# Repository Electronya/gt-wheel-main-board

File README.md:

# gt-wheel-main-board
GT DIY Wheel Main Board

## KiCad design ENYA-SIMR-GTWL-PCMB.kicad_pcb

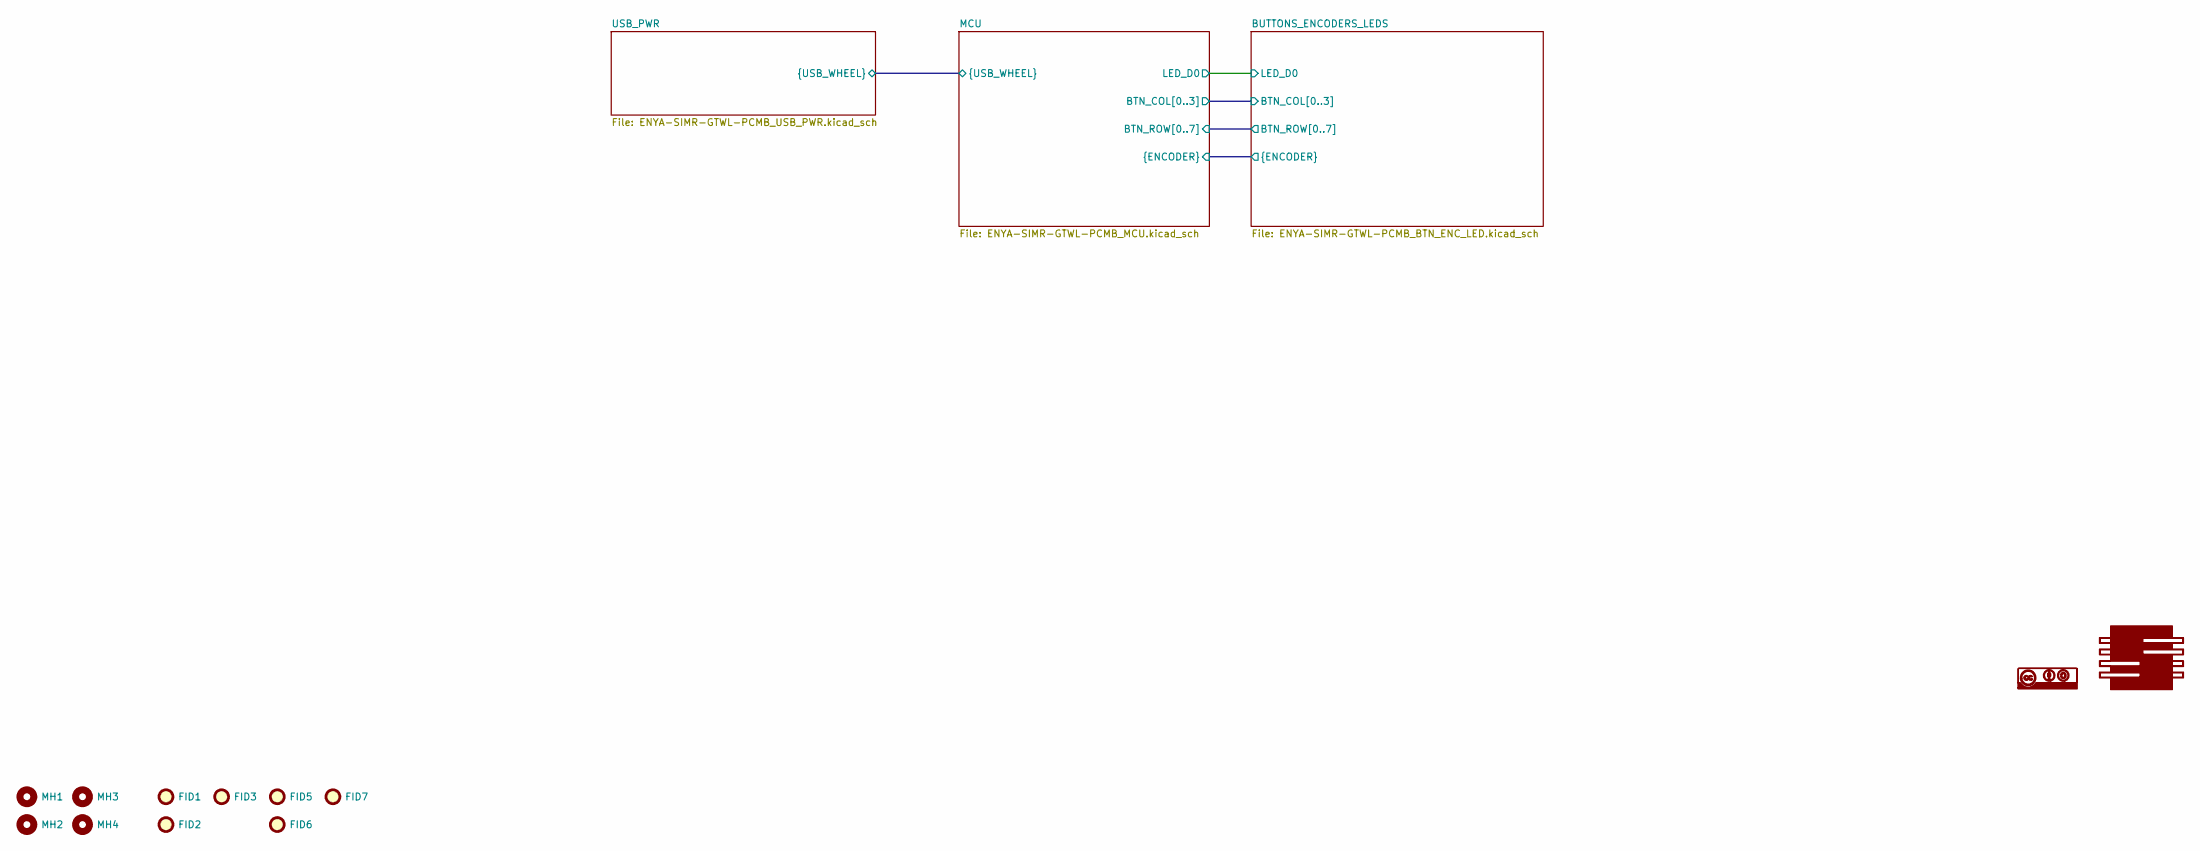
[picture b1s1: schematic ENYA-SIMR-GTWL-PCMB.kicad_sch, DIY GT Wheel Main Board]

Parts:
FID1, FID2, FID3, FID5, FID6, FID7: Fiducial; Fiducial_1.5mm_Mask3mm
G1: Electronya_Logo; Electronya_Logo_12MM
G2: CC-BY-SA_Logo; CC-BY-SA_10MM
MH1, MH2, MH3, MH4: MH-NPLTD-M3; MountingHole_3.2mm_M3_DIN965

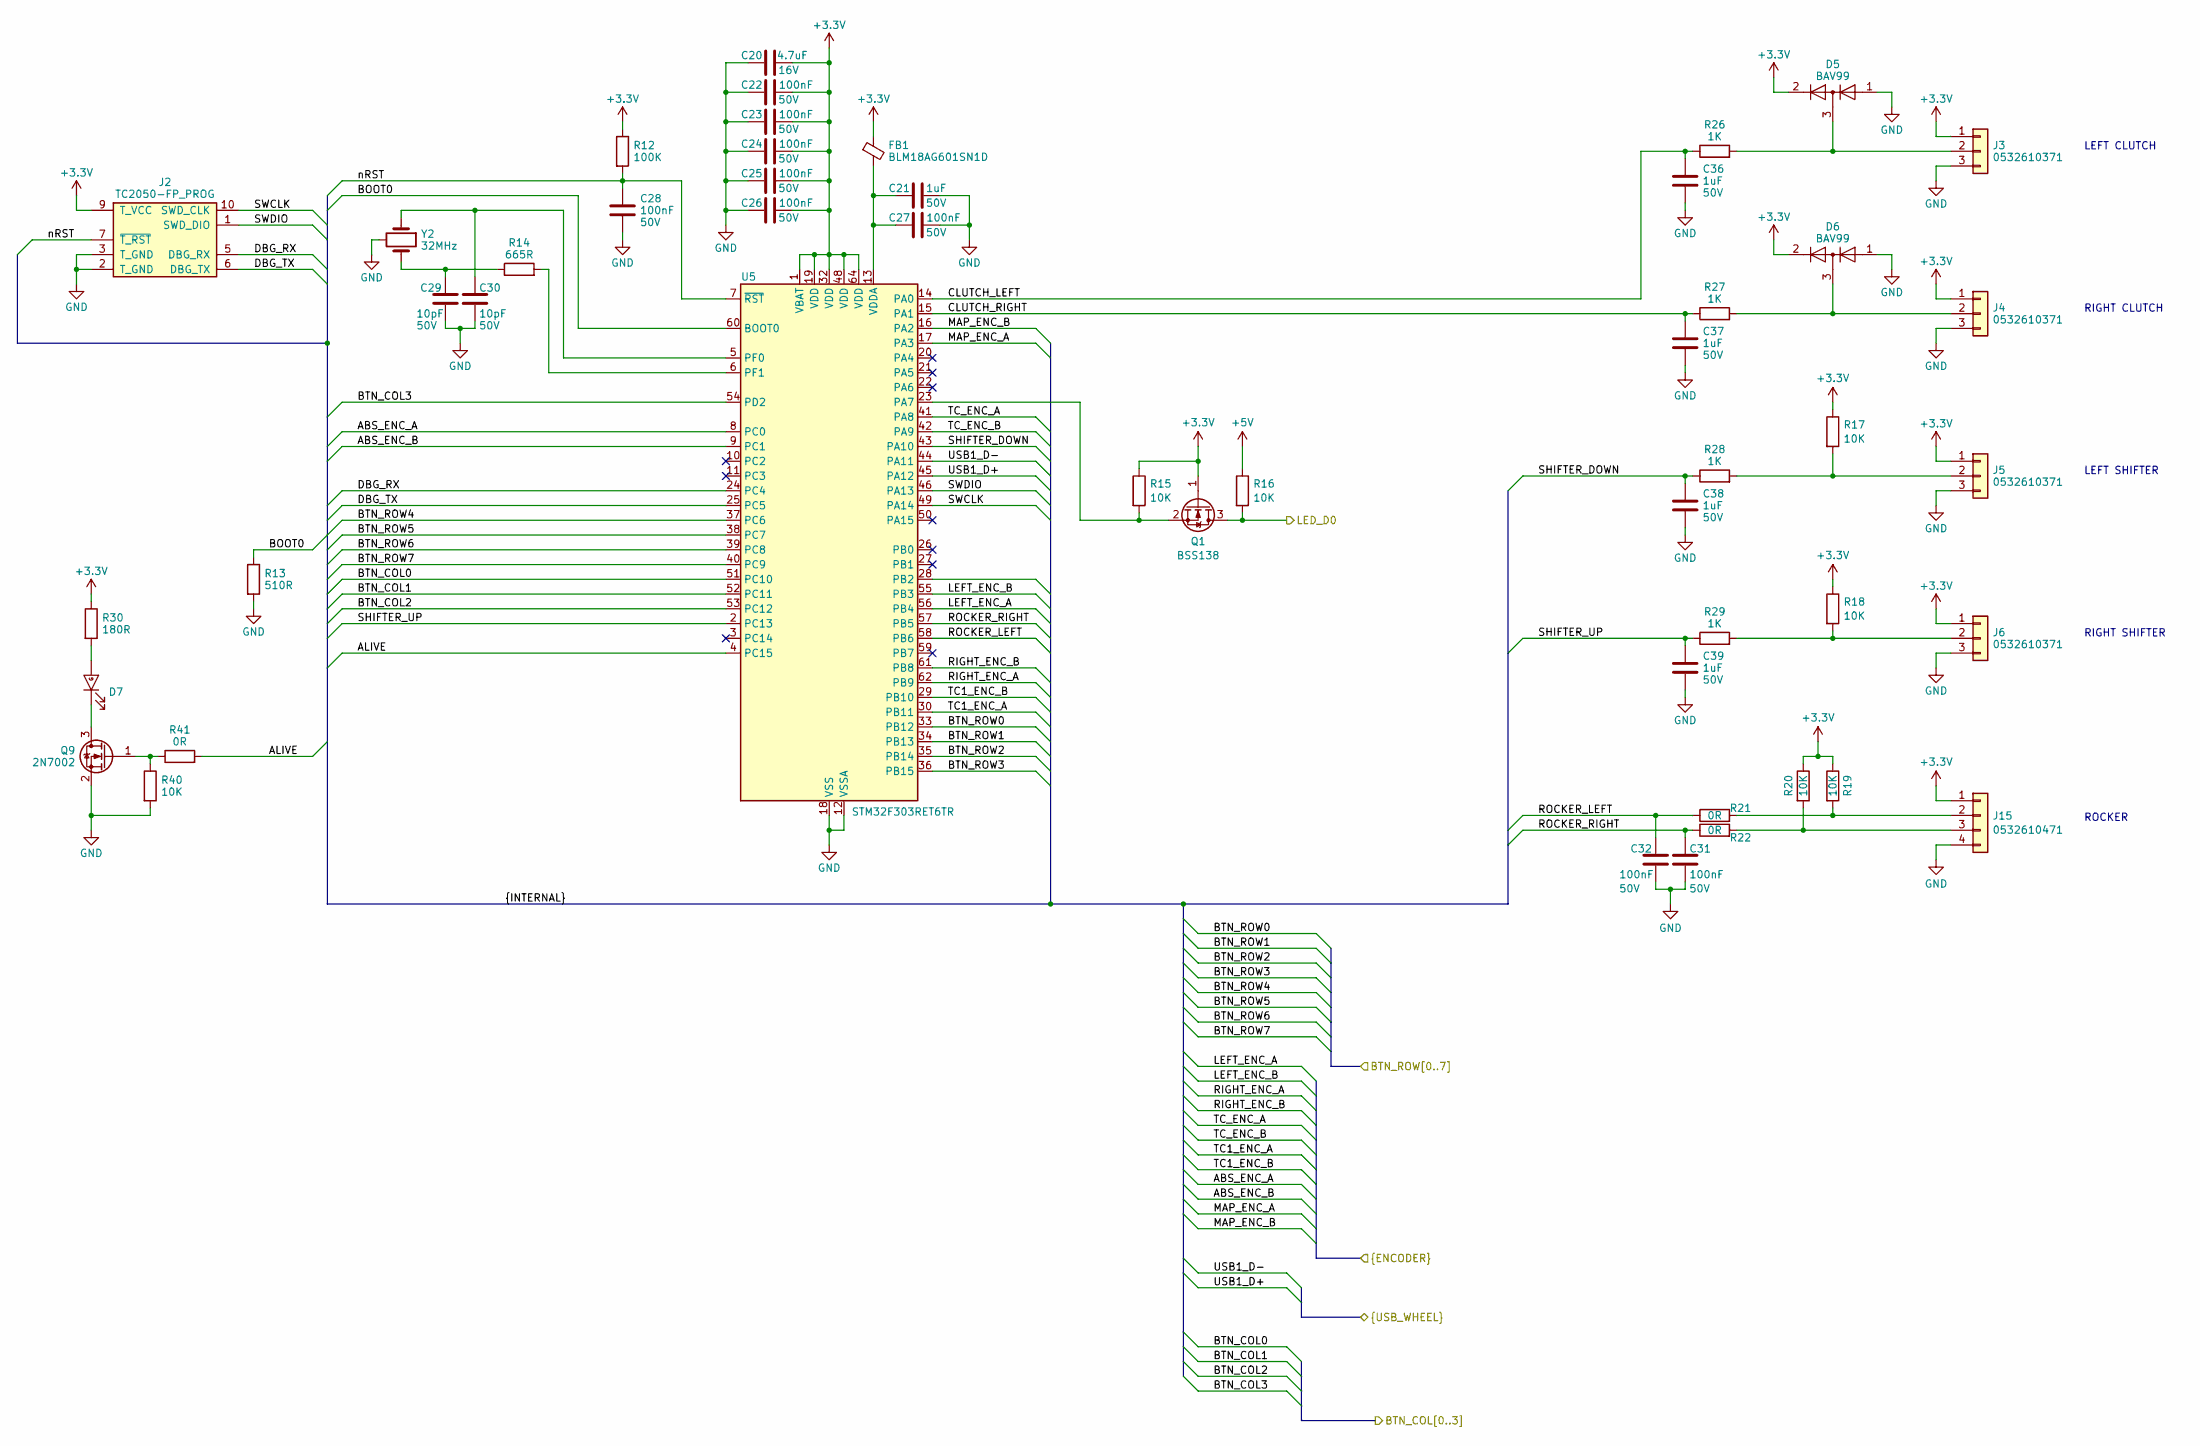
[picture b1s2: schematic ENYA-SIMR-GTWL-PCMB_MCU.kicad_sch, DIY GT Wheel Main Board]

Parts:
C20: 4.7uF_CER_0805_16V; C_0805_2012Metric; Voltage Rating 16V; Manufacturer Part Number CL21B475KOFNNNE; Digi-Key Part Number 1276-2873-1-ND
C21, C36, C37, C38, C39: 1uF_CER_0603_50V; C_0603_1608Metric; Voltage Rating 50V; Manufacturer Part Number UMK107BJ105KA-T; Digi-Key Part Number 587-2400-1-ND
C22, C23, C24, C25, C26, C27, C28, C31, C32: 100nF_CER_0603_50V; C_0603_1608Metric; Voltage Rating 50V; Manufacturer Part Number 06033D104MAT2A; Digi-Key Part Number 478-7905-1-ND
C29, C30: 10pF_CER_0603_50V; C_0603_1608Metric; Voltage Rating 50V; Manufacturer Part Number 06035A100JAT2A; Digi-Key Part Number 478-1163-1-ND
D5: BAV99; SOT-23
D6: BAV99_SOT-23; SOT-23; Manufacturer Part Number BAV99; Digi-Key Part Number 1655-BAV99CT-ND
D7: GRN_SMD_0603_0.3H; LED_0603_1608Metric; Manufacturer Part Number 150060GS73220; Digi-Key Part Number 732-11995-1-ND
FB1: 600R_100MHz_0R38_0603; L_0603_1608Metric; Manufacturer Part Number BLM18AG601SN1D; Digi-Key Part Number 490-1014-1-ND
J2: TC2050-FP_PROG; Tag-Connect_TC2050-IDC-FP_2x05_P1.27mm_Vertical; Manufacturer Part Number TC2050-FP
J3, J4, J5, J6: PICO_BLADE_1x3_MALE_RA_SMD; PICO_BLADE_53261_1x3_SMD_RA_1.25MM; Manufacturer Part Number 0532610371; Digi-Key Part Number WM7621CT-ND
J15: PICO_BLADE_1x4_MALE_RA_SMD; PICO_BLADE_53261_1x4_SMD_RA_1.25MM; Manufacturer Part Number 0532610471; Digi-Key Part Number WM7622CT-ND
Q1: BSS138; SOT-23; Manufacturer Part Number BSS138; Digi-Key Part Number BSS138CT-ND
Q9: 2N7002; SOT-23; Manufacturer Part Number 2N7002; Digi-Key Part Number 2N7002NCT-ND
R12: 100K_0603_100MW; R_0603_1608Metric; Manufacturer Part Number RC0603FR-07100KL; Digi-Key Part Number 311-100KHRCT-ND
R13: 510R_0603_100MW; R_0603_1608Metric; Manufacturer Part Number RC0603FR-07510RL; Digi-Key Part Number 311-510HRCT-ND
R14: 665R_0603_100MW; R_0603_1608Metric; Manufacturer Part Number RC0603FR-07665RL; Digi-Key Part Number 311-665HRCT-ND
R15, R16, R17, R18, R19, R20, R40: 10K_0603_100MW; R_0603_1608Metric; Manufacturer Part Number ERJ-3EKF1002V; Digi-Key Part Number P10.0KHCT-ND
R21, R22, R41: 0R_0603_100MW; R_0603_1608Metric; Manufacturer Part Number ERJ-3GEY0R00V; Digi-Key Part Number P0.0GCT-ND
R26, R27, R28, R29: 1K_0603_100MW; R_0603_1608Metric; Manufacturer Part Number ERJ-3EKF1001V; Digi-Key Part Number P1.00KHCT-ND
R30: 180R_0603_100MW; R_0603_1608Metric; Manufacturer Part Number RC0603FR-07180RL; Digi-Key Part Number 311-180HRCT-ND
U5: STM32F303RET6TR; LQFP-64_10x10mm_P0.5mm; Manufacturer Part Number STM32F303RET6TR; Digi-Key Part Number 497-18778-1-ND
Y2: ABM10_32MHz_10pF_SMD4_2.5x2.0; ABM10_SMD4_2.5x2.0mm; Manufacturer Part Number ABM10-32.000MHZ-D30-T3; Digi-Key Part Number 535-10936-1-ND

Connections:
+3.3V: C20.2, C22.2, C23.2, C24.2, C25.2, C26.2, D5.2 (A), D6.2 (A), FB1.1, J2.9 (T_VCC), J3.1, J4.1, J5.1, J6.1, J15.1, Q1.1 (G), R12.1, R15.1, R17.1, R18.1, R19.1, R20.1, R30.1, U5.1 (VBAT), U5.19 (VDD), U5.32 (VDD), U5.48 (VDD), U5.64 (VDD); also elsewhere on the board
+5V: R16.1; also elsewhere on the board
/BUTTONS_ENCODERS_LEDS/ABS_ENC_A: U5.8 (PC0); also elsewhere on the board
/BUTTONS_ENCODERS_LEDS/ABS_ENC_B: U5.9 (PC1); also elsewhere on the board
/BUTTONS_ENCODERS_LEDS/BTN_COL0: U5.51 (PC10); also elsewhere on the board
/BUTTONS_ENCODERS_LEDS/BTN_COL1: U5.52 (PC11); also elsewhere on the board
/BUTTONS_ENCODERS_LEDS/BTN_COL2: U5.53 (PC12); also elsewhere on the board
/BUTTONS_ENCODERS_LEDS/BTN_COL3: U5.54 (PD2); also elsewhere on the board
/BUTTONS_ENCODERS_LEDS/BTN_ROW0: U5.33 (PB12); also elsewhere on the board
/BUTTONS_ENCODERS_LEDS/BTN_ROW1: U5.34 (PB13); also elsewhere on the board
/BUTTONS_ENCODERS_LEDS/BTN_ROW2: U5.35 (PB14); also elsewhere on the board
/BUTTONS_ENCODERS_LEDS/BTN_ROW3: U5.36 (PB15); also elsewhere on the board
/BUTTONS_ENCODERS_LEDS/BTN_ROW4: U5.37 (PC6); also elsewhere on the board
/BUTTONS_ENCODERS_LEDS/BTN_ROW5: U5.38 (PC7); also elsewhere on the board
/BUTTONS_ENCODERS_LEDS/BTN_ROW6: U5.39 (PC8); also elsewhere on the board
/BUTTONS_ENCODERS_LEDS/BTN_ROW7: U5.40 (PC9); also elsewhere on the board
/BUTTONS_ENCODERS_LEDS/LED_D0: Q1.3 (D), R16.2; also elsewhere on the board
/BUTTONS_ENCODERS_LEDS/LEFT_ENC_A: U5.56 (PB4); also elsewhere on the board
/BUTTONS_ENCODERS_LEDS/LEFT_ENC_B: U5.55 (PB3); also elsewhere on the board
/BUTTONS_ENCODERS_LEDS/MAP_ENC_A: U5.17 (PA3); also elsewhere on the board
/BUTTONS_ENCODERS_LEDS/MAP_ENC_B: U5.16 (PA2); also elsewhere on the board
/BUTTONS_ENCODERS_LEDS/RIGHT_ENC_A: U5.62 (PB9); also elsewhere on the board
/BUTTONS_ENCODERS_LEDS/RIGHT_ENC_B: U5.61 (PB8); also elsewhere on the board
/BUTTONS_ENCODERS_LEDS/TC1_ENC_A: U5.30 (PB11); also elsewhere on the board
/BUTTONS_ENCODERS_LEDS/TC1_ENC_B: U5.29 (PB10); also elsewhere on the board
/BUTTONS_ENCODERS_LEDS/TC_ENC_A: U5.41 (PA8); also elsewhere on the board
/BUTTONS_ENCODERS_LEDS/TC_ENC_B: U5.42 (PA9); also elsewhere on the board
/MCU/ALIVE: R41.2, U5.4 (PC15)
/MCU/BOOT0: R13.1, U5.60 (BOOT0)
/MCU/CLUTCH_LEFT: C36.1, R26.1, U5.14 (PA0)
/MCU/CLUTCH_RIGHT: C37.1, R27.1, U5.15 (PA1)
/MCU/DBG_RX: J2.5 (DBG_RX), U5.24 (PC4)
/MCU/DBG_TX: J2.6 (DBG_TX), U5.25 (PC5)
/MCU/ROCKER_LEFT: C32.1, R21.1, U5.58 (PB6)
/MCU/ROCKER_RIGHT: C31.1, R22.1, U5.57 (PB5)
/MCU/SHIFTER_DOWN: C38.1, R28.1, U5.43 (PA10)
/MCU/SHIFTER_UP: C39.1, R29.1, U5.2 (PC13)
/MCU/SWCLK: J2.10 (SWD_CLK), U5.49 (PA14)
/MCU/SWDIO: J2.1 (SWD_DIO), U5.46 (PA13)
/MCU/USB1_D+: U5.45 (PA12); also elsewhere on the board
/MCU/USB1_D-: U5.44 (PA11); also elsewhere on the board
/MCU/nRST: C28.1, J2.7 (~T_RST), R12.2, U5.7 (~RST)
GND: C20.1, C21.2, C22.1, C23.1, C24.1, C25.1, C26.1, C27.2, C28.2, C29.2, C30.2, C31.2, C32.2, C36.2, C37.2, C38.2, C39.2, D5.1 (K), D6.1 (K), J2.2 (T_GND), J2.3 (T_GND), J3.3, J4.3, J5.3, J6.3, J15.4, Q9.2 (S), R13.2, R40.2, U5.12 (VSSA), U5.18 (VSS), U5.31 (VSS), U5.47 (VSS), U5.63 (VSS), Y2.2 (GND), Y2.4 (GND); also elsewhere on the board
unnamed: C29.1, R14.1, Y2.3
unnamed: D7.2 (A), R30.2
unnamed: D7.1 (K), Q9.3 (D)
unnamed: D5.3 (K), J3.2, R26.2
unnamed: D6.3 (K), J4.2, R27.2
unnamed: J5.2, R17.2, R28.2
unnamed: J6.2, R18.2, R29.2
unnamed: J15.2, R19.2, R21.2
unnamed: J15.3, R20.2, R22.2
unnamed: Q1.2 (S), R15.2, U5.23 (PA7)
unnamed: Q9.1 (G), R40.1, R41.1
unnamed: C30.1, U5.5 (PF0), Y2.1
unnamed: R14.2, U5.6 (PF1)
unnamed: C21.1, C27.1, FB1.2, U5.13 (VDDA)

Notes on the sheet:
RIGHT CLUTCH
RIGHT SHIFTER
ROCKER
LEFT SHIFTER
LEFT CLUTCH

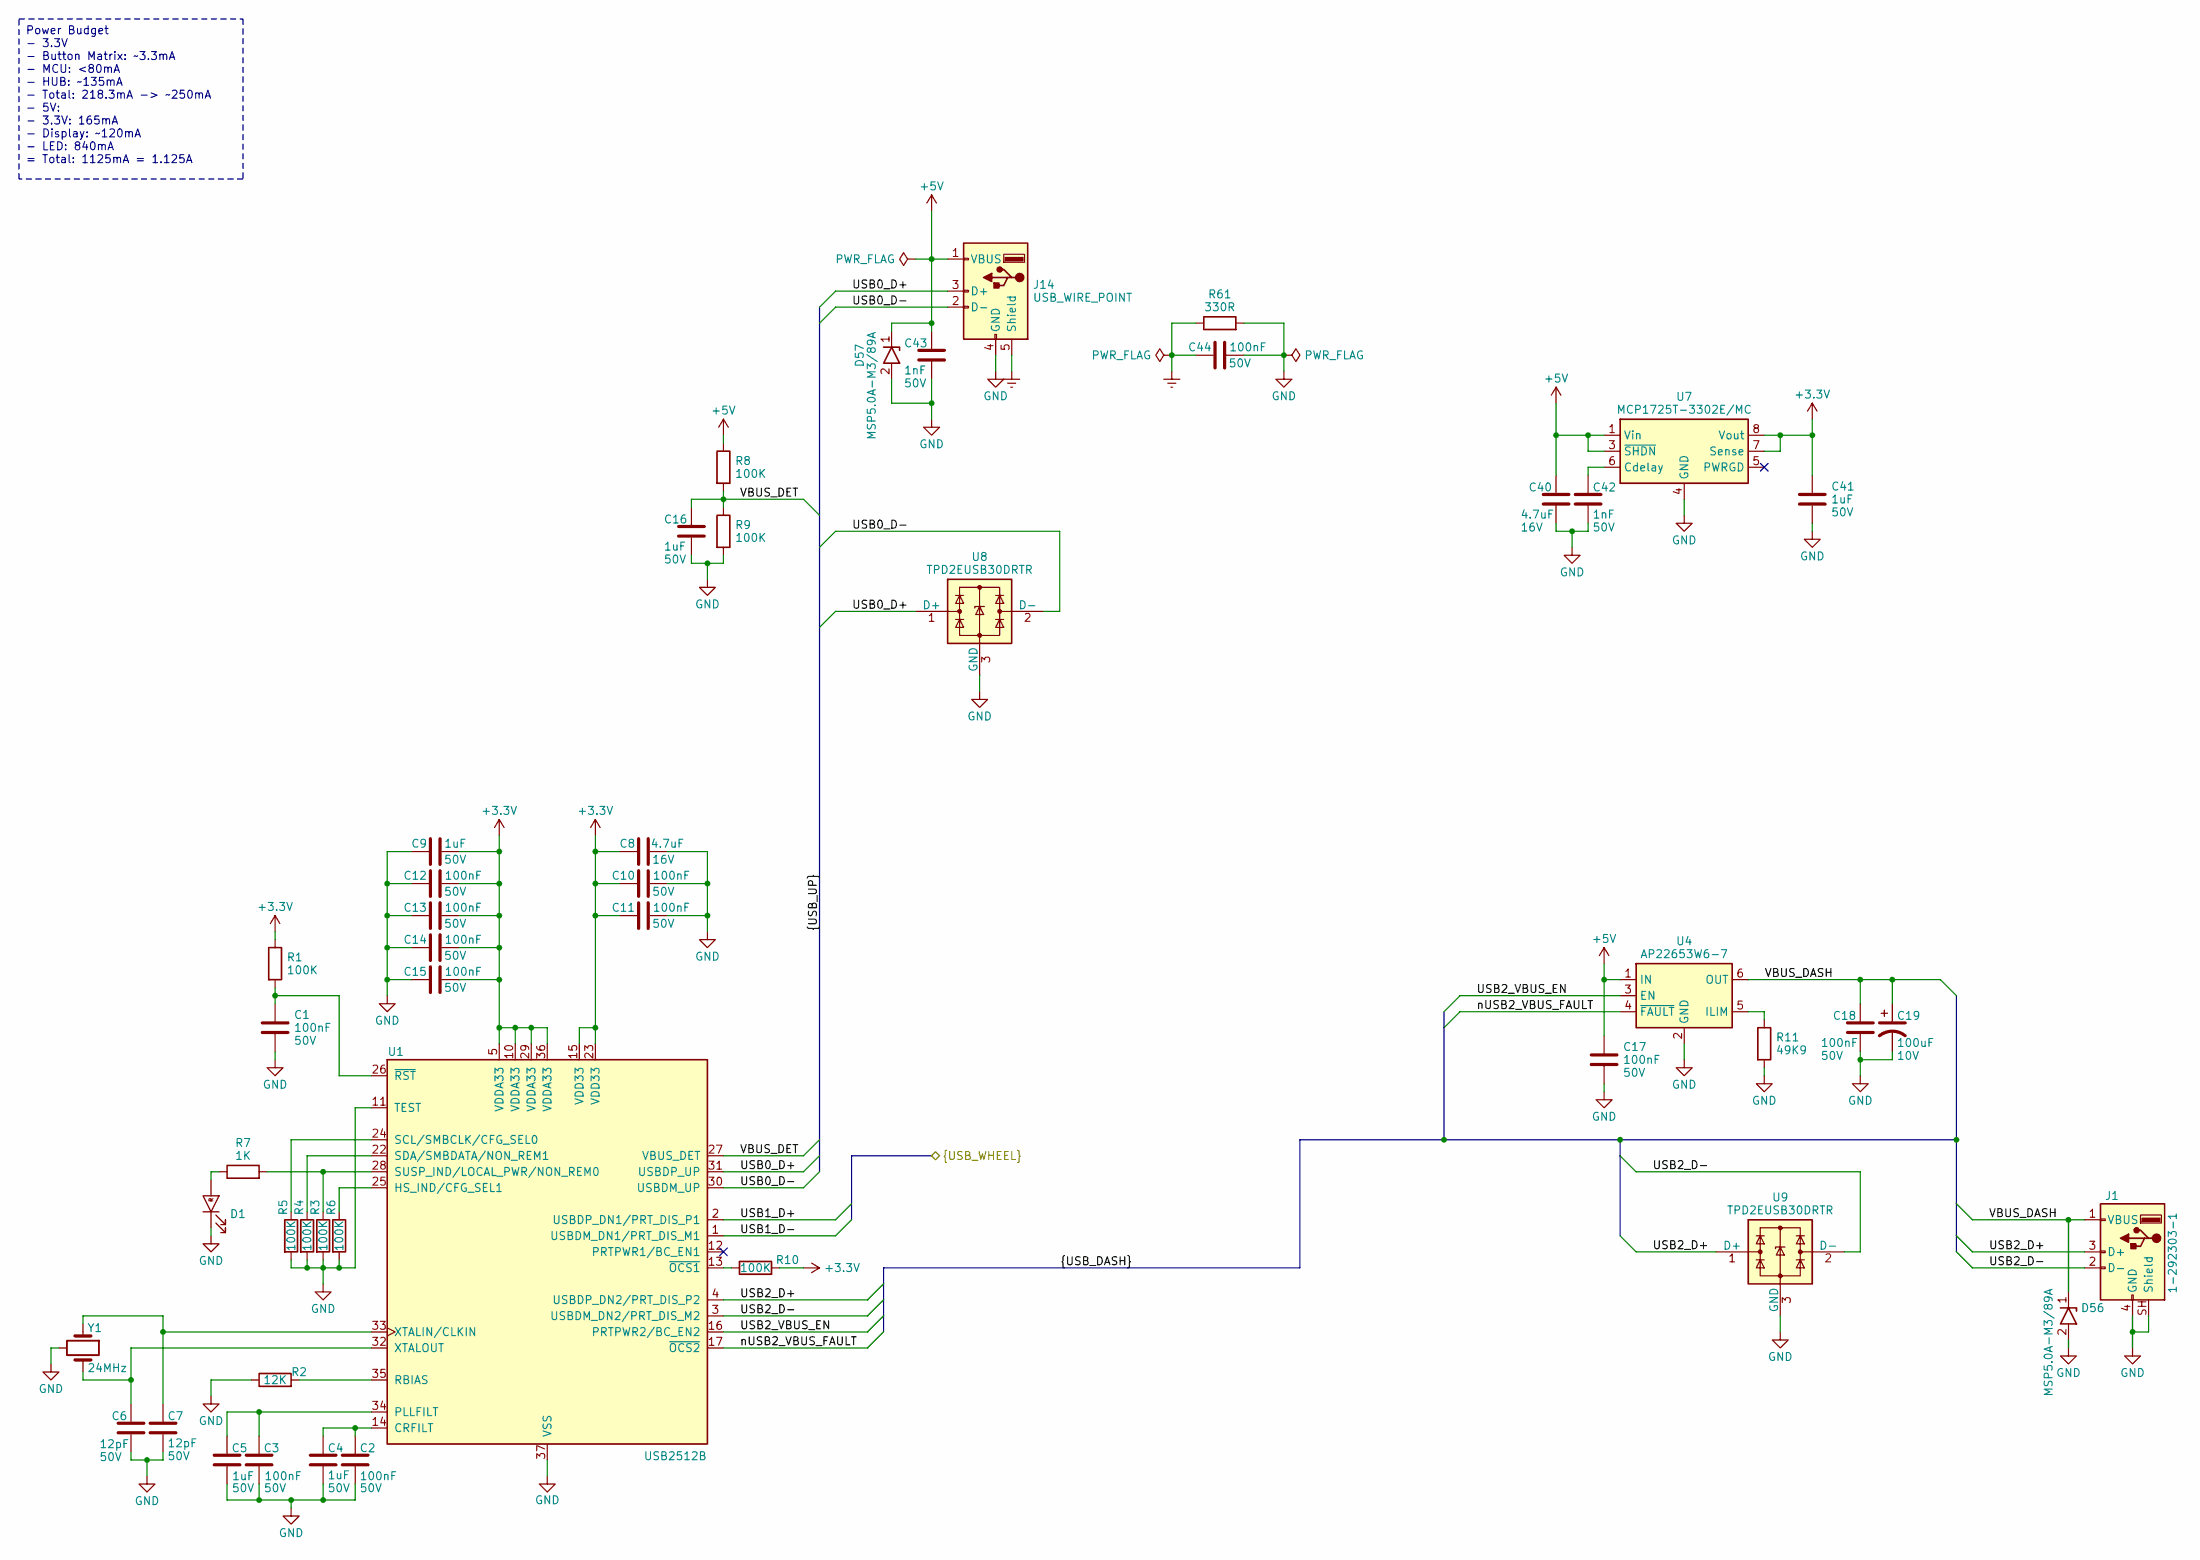
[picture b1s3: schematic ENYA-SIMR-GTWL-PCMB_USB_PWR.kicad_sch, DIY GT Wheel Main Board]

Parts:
C1, C2, C3, C10, C11, C12, C13, C14, C15, C17, C18, C44: 100nF_CER_0603_50V; C_0603_1608Metric; Voltage Rating 50V; Manufacturer Part Number 06033D104MAT2A; Digi-Key Part Number 478-7905-1-ND
C4, C5, C9, C16, C41: 1uF_CER_0603_50V; C_0603_1608Metric; Voltage Rating 50V; Manufacturer Part Number UMK107BJ105KA-T; Digi-Key Part Number 587-2400-1-ND
C6, C7: 12pF_CER_0603_50V; C_0603_1608Metric; Voltage Rating 50V; Manufacturer Part Number CGA3E2C0G1H120J080AA; Digi-Key Part Number 445-5629-1-ND
C8, C40: 4.7uF_CER_0805_16V; C_0805_2012Metric; Voltage Rating 16V; Manufacturer Part Number CL21B475KOFNNNE; Digi-Key Part Number 1276-2873-1-ND
C19: 100UF_TANT_2917_10V; CP_EIA-7343-15_Kemet-W; Voltage Rating 10V; Manufacturer Part Number TAJD107M010RNJ; Digi-Key Part Number 478-3918-1-ND
C42, C43: 1nF_CER_0603_50V; C_0603_1608Metric; Voltage Rating 50V; Manufacturer Part Number C0603C102K5RAC7867; Digi-Key Part Number 399-C0603C102K5RAC7867CT-ND
D1: RED_SMD_0603_0.3H; LED_0603_1608Metric; Manufacturer Part Number 150060RS75000; Digi-Key Part Number 732-4978-1-ND
D56, D57: MSP5.0A_5V_9.2V_D0-219AD; DO-219AD; Manufacturer Part Number MSP5.0A-M3/89A; Digi-Key Part Number MSP5.0A-M3/89AGICT-ND
J1: USB_A_RA; Manufacturer Part Number 1-292303-1; Digi-Key Part Number A127890-ND
J14: USB_WIRE_POINT
R1, R3, R4, R5, R6, R8, R9, R10: 100K_0603_100MW; R_0603_1608Metric; Manufacturer Part Number RC0603FR-07100KL; Digi-Key Part Number 311-100KHRCT-ND
R2: 12K_0603_100MW; R_0603_1608Metric; Manufacturer Part Number RC0603FR-0712KL; Digi-Key Part Number 311-12.0KHRCT-ND
R7: 1K_0603_100MW; R_0603_1608Metric; Manufacturer Part Number ERJ-3EKF1001V; Digi-Key Part Number P1.00KHCT-ND
R11: 49K9_0603_100MW; R_0603_1608Metric; Manufacturer Part Number CRCW060349K9FKEAC; Digi-Key Part Number 541-3989-1-ND
R61: 330R_0603_100MW; R_0603_1608Metric; Manufacturer Part Number RC0603FR-07330RL; Digi-Key Part Number 311-330HRCT-ND
U1: USB2512B; QFN-36-1EP_6x6mm_P0.5mm_EP3.7x3.7mm; Manufacturer Part Number USB2512B-AEZG-TR; Digi-Key Part Number USB2512B-AEZG-CT-ND
U4: AP22653W6-7_ILIM_2.1A_SOT-23-6; SOT-23-6; Manufacturer Part Number AP22653W6-7; Digi-Key Part Number 31-AP22653W6-7CT-ND
U7: MCP1725_3.3V_500mA_DFN-8; DFN-8-1EP_3x2mm_P0.5mm_EP1.75x1.45mm; Manufacturer Part Number MCP1725T-3302E/MC; Digi-Key Part Number MCP1725T-3302E/MCCT-ND
U8, U9: TPD2EUSB30_5.5V_8V_SOT-3; Texas_DRT-3; Manufacturer PArt Number TPD2EUSB30DRTR; Digi-Key Part Number 296-25509-1-ND
Y1: ABM10_24MHz_10pF_SMD4_2.5x2.0; ABM10_SMD4_2.5x2.0mm; Manufacturer Part Number ABM10-24.000MHZ-E20-T; Digi-Key Part Number 535-9093-1-ND

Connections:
+3.3V: C8.1, C9.2, C10.1, C11.1, C12.2, C13.2, C14.2, C15.2, C41.1, R1.1, R10.2, U1.5 (VDDA33), U1.10 (VDDA33), U1.15 (VDD33), U1.23 (VDD33), U1.29 (VDDA33), U1.36 (VDDA33), U7.7 (Sense), U7.8 (Vout); also elsewhere on the board
+5V: C17.1, C40.1, C43.1, D57.1 (A1), J14.1 (VBUS), R8.1, U4.1 (IN), U7.1 (Vin), U7.2 (Vin), U7.3 (~SHDN); also elsewhere on the board
/MCU/USB1_D+: U1.2 (USBDP_DN1/PRT_DIS_P1); also elsewhere on the board
/MCU/USB1_D-: U1.1 (USBDM_DN1/PRT_DIS_M1); also elsewhere on the board
/USB_PWR/USB0_D+: J14.3 (D+), U1.31 (USBDP_UP), U8.1 (D+)
/USB_PWR/USB0_D-: J14.2 (D-), U1.30 (USBDM_UP), U8.2 (D-)
/USB_PWR/USB2_D+: J1.3 (D+), U1.4 (USBDP_DN2/PRT_DIS_P2), U9.1 (D+)
/USB_PWR/USB2_D-: J1.2 (D-), U1.3 (USBDM_DN2/PRT_DIS_M2), U9.2 (D-)
/USB_PWR/USB2_VBUS_EN: U1.16 (PRTPWR2/BC_EN2), U4.3 (EN)
/USB_PWR/VBUS_DASH: C18.1, C19.1, D56.1 (A1), J1.1 (VBUS), U4.6 (OUT)
/USB_PWR/VBUS_DET: C16.1, R8.2, R9.1, U1.27 (VBUS_DET)
/USB_PWR/nUSB2_VBUS_FAULT: U1.17 (~OCS2), U4.4 (~FAULT)
Earth: C44.1, J14.5 (Shield), R61.1
GND: C1.2, C2.2, C3.2, C4.2, C5.2, C6.2, C7.2, C8.2, C9.1, C10.2, C11.2, C12.1, C13.1, C14.1, C15.1, C16.2, C17.2, C18.2, C19.2, C40.2, C41.2, C42.2, C43.2, C44.2, D1.1 (K), D56.2 (A2), D57.2 (A2), J1.4 (GND), J1.SH (Shield), J14.4 (GND), R2.1, R3.2, R4.2, R5.2, R6.2, R9.2, R11.2, R61.2, U1.11 (TEST), U1.37 (VSS), U4.2 (GND), U7.4 (GND), U7.9 (GND), U8.3 (GND), U9.3 (GND), Y1.2 (GND), Y1.4 (GND); also elsewhere on the board
unnamed: D1.2 (A), R7.1
unnamed: C2.1, C4.1, U1.14 (CRFILT)
unnamed: R6.1, U1.25 (HS_IND/CFG_SEL1)
unnamed: C3.1, C5.1, U1.34 (PLLFILT)
unnamed: R2.2, U1.35 (RBIAS)
unnamed: R5.1, U1.24 (SCL/SMBCLK/CFG_SEL0)
unnamed: R4.1, U1.22 (SDA/SMBDATA/NON_REM1)
unnamed: R3.1, R7.2, U1.28 (SUSP_IND/LOCAL_PWR/NON_REM0)
unnamed: C7.1, U1.33 (XTALIN/CLKIN), Y1.1
unnamed: C6.1, U1.32 (XTALOUT), Y1.3
unnamed: R10.1, U1.13 (~OCS1)
unnamed: C1.1, R1.2, U1.26 (~RST)
unnamed: R11.1, U4.5 (ILIM)
unnamed: C42.1, U7.6 (Cdelay)

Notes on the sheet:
Power Budget - 3.3V - Button Matrix: ~3.3mA - MCU: <80mA - HUB: ~135mA - Total: 218.3mA -> ~250mA - 5V: - 3.3V: 165mA - Display: ~120mA - LED: 840mA = Total: 1125mA = 1.125A

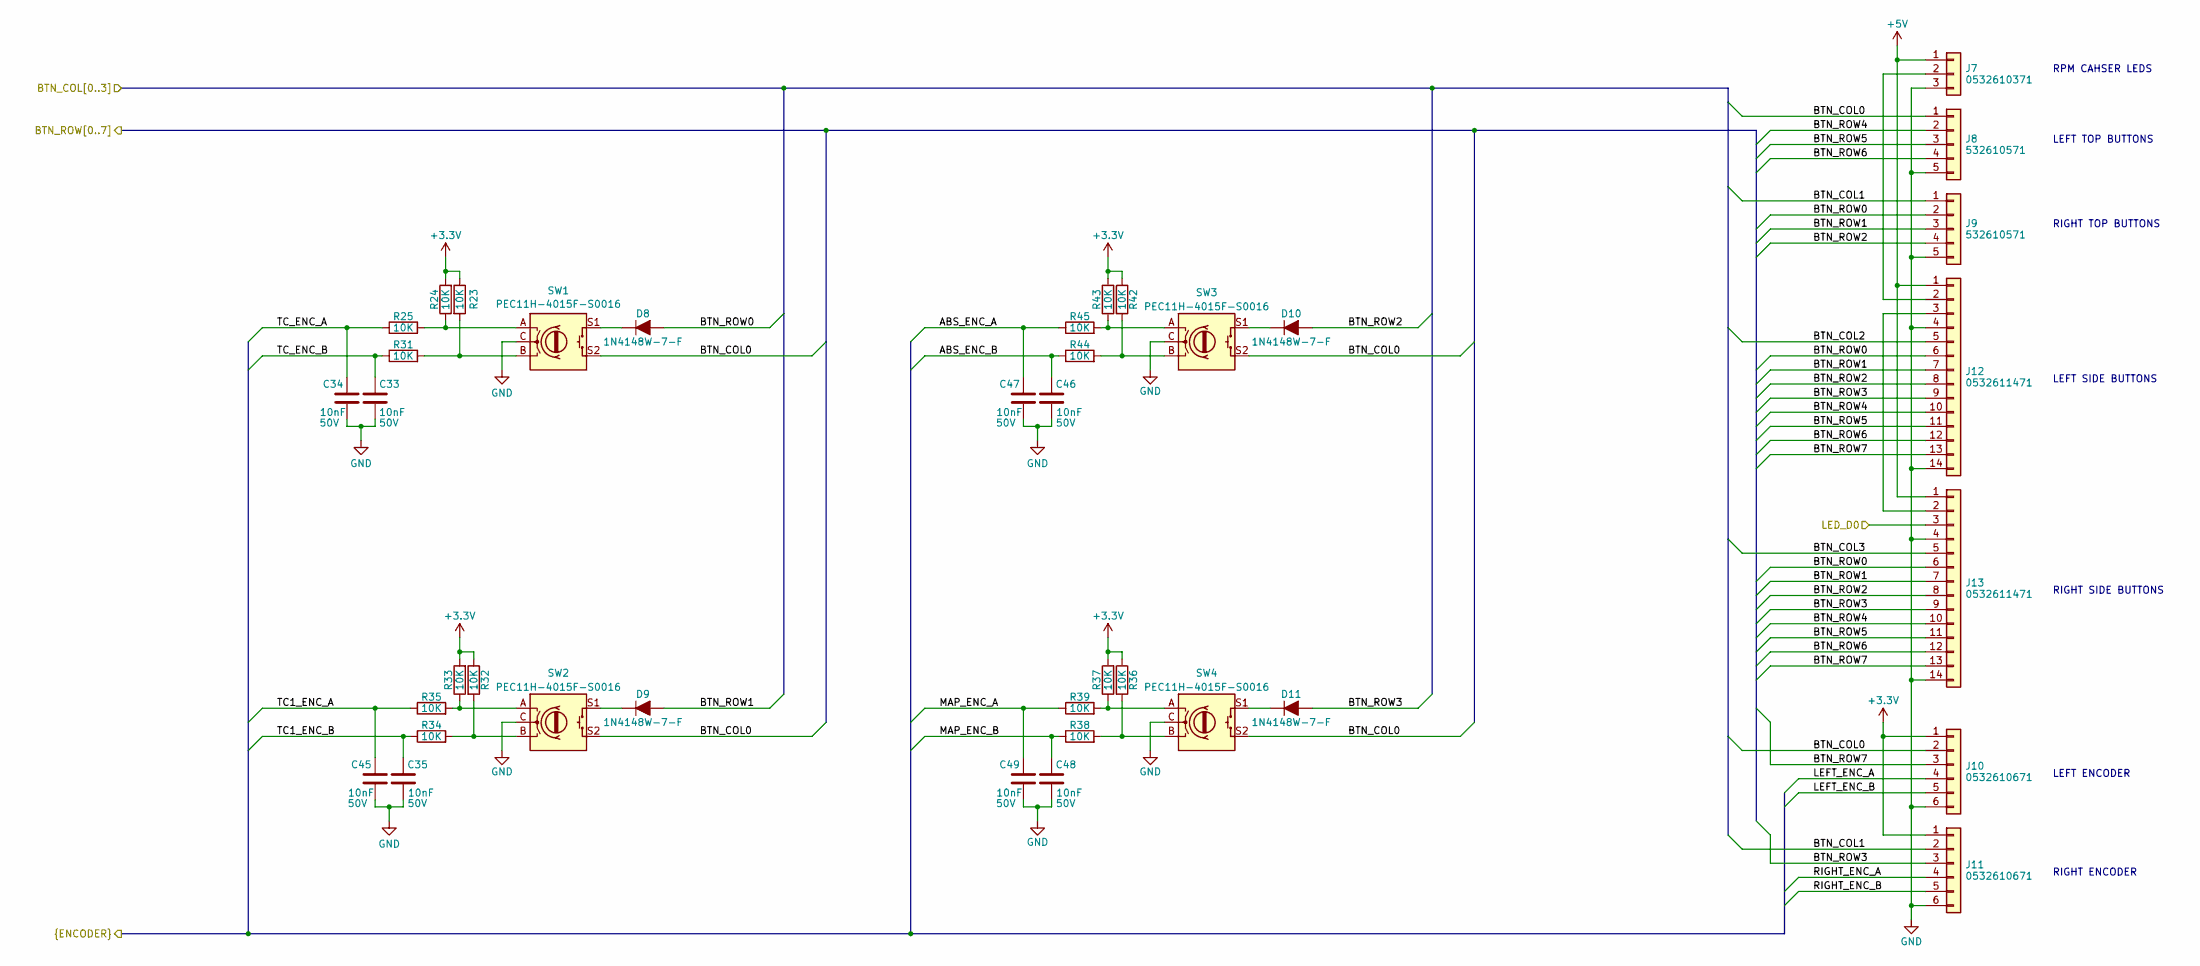
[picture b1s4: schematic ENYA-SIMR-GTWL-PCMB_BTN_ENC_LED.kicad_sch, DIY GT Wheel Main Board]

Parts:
C33, C34, C35, C45, C46, C47, C48, C49: 10nF_CER_0603_50V; C_0603_1608Metric; Voltage Rating 50V; Manufacturer Part Number 06035C103KAT2A; Digi-Key Part Number 478-1227-1-ND
D8, D9, D10, D11: 1N4148W-7-F; D_SOD-123; Manufacturer Part Number 1N4148W-7-F; Digi-Key Part Number 1N4148W-FDICT-ND
J7: PICO_BLADE_1x3_MALE_RA_SMD; PICO_BLADE_53261_1x3_SMD_RA_1.25MM; Manufacturer Part Number 0532610371; Digi-Key Part Number WM7621CT-ND
J8, J9: PICO_BLADE_1x5_MALE_RA_SMD; PICO_BLADE_53261_1x5_SMD_RA_1.25MM; Manufacturer Part Number 532610571; Digi-Key Part Number WM7623CT-ND
J10, J11: PICO_BLADE_1x6_MALE_RA_SMD; PICO_BLADE_53261_1x6_SMD_RA_1.25MM; Manufacturer Part Number 0532610671; Digi-Key Part Number WM7624CT-ND
J12, J13: PICO_BLADE_1x14_MALE_RA_SMD; PICO_BLADE_53261_1x14_SMD_RA_1.25MM; Manufacturer Part Number 0532611471; Digi-Key Part Number WM7631CT-ND
R23, R24, R25, R31, R32, R33, R34, R35, R36, R37, R38, R39, R42, R43, R44, R45: 10K_0603_100MW; R_0603_1608Metric; Manufacturer Part Number ERJ-3EKF1002V; Digi-Key Part Number P10.0KHCT-ND
SW1, SW2, SW3, SW4: PEC11H-4015F-S0016; PEC11H_Switch_Vertical; Manufacturer Part Number PEC11H-4015F-S0016; Digi-Key Part Number 118-PEC11H-4015F-S0016-ND

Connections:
+3.3V: J10.1, J11.1, R23.1, R24.2, R32.1, R33.2, R36.1, R37.2, R42.1, R43.2; also elsewhere on the board
+5V: J7.1, J12.1, J13.1; also elsewhere on the board
/BUTTONS_ENCODERS_LEDS/ABS_ENC_A: C47.1, R45.1; also elsewhere on the board
/BUTTONS_ENCODERS_LEDS/ABS_ENC_B: C46.1, R44.1; also elsewhere on the board
/BUTTONS_ENCODERS_LEDS/BTN_COL0: J8.1, J10.2, SW1.S2, SW2.S2, SW3.S2, SW4.S2; also elsewhere on the board
/BUTTONS_ENCODERS_LEDS/BTN_COL1: J9.1, J11.2; also elsewhere on the board
/BUTTONS_ENCODERS_LEDS/BTN_COL2: J12.5; also elsewhere on the board
/BUTTONS_ENCODERS_LEDS/BTN_COL3: J13.5; also elsewhere on the board
/BUTTONS_ENCODERS_LEDS/BTN_ROW0: D8.2 (A), J9.2, J12.6, J13.6; also elsewhere on the board
/BUTTONS_ENCODERS_LEDS/BTN_ROW1: D9.2 (A), J9.3, J12.7, J13.7; also elsewhere on the board
/BUTTONS_ENCODERS_LEDS/BTN_ROW2: D10.2 (A), J9.4, J12.8, J13.8; also elsewhere on the board
/BUTTONS_ENCODERS_LEDS/BTN_ROW3: D11.2 (A), J11.3, J12.9, J13.9; also elsewhere on the board
/BUTTONS_ENCODERS_LEDS/BTN_ROW4: J8.2, J12.10, J13.10; also elsewhere on the board
/BUTTONS_ENCODERS_LEDS/BTN_ROW5: J8.3, J12.11, J13.11; also elsewhere on the board
/BUTTONS_ENCODERS_LEDS/BTN_ROW6: J8.4, J12.12, J13.12; also elsewhere on the board
/BUTTONS_ENCODERS_LEDS/BTN_ROW7: J10.3, J12.13, J13.13; also elsewhere on the board
/BUTTONS_ENCODERS_LEDS/LED_D0: J13.3; also elsewhere on the board
/BUTTONS_ENCODERS_LEDS/LEFT_ENC_A: J10.4; also elsewhere on the board
/BUTTONS_ENCODERS_LEDS/LEFT_ENC_B: J10.5; also elsewhere on the board
/BUTTONS_ENCODERS_LEDS/MAP_ENC_A: C49.1, R39.1; also elsewhere on the board
/BUTTONS_ENCODERS_LEDS/MAP_ENC_B: C48.1, R38.1; also elsewhere on the board
/BUTTONS_ENCODERS_LEDS/RIGHT_ENC_A: J11.4; also elsewhere on the board
/BUTTONS_ENCODERS_LEDS/RIGHT_ENC_B: J11.5; also elsewhere on the board
/BUTTONS_ENCODERS_LEDS/TC1_ENC_A: C45.1, R35.1; also elsewhere on the board
/BUTTONS_ENCODERS_LEDS/TC1_ENC_B: C35.1, R34.1; also elsewhere on the board
/BUTTONS_ENCODERS_LEDS/TC_ENC_A: C34.1, R25.1; also elsewhere on the board
/BUTTONS_ENCODERS_LEDS/TC_ENC_B: C33.1, R31.1; also elsewhere on the board
GND: C33.2, C34.2, C35.2, C45.2, C46.2, C47.2, C48.2, C49.2, J7.3, J8.5, J9.5, J10.6, J11.6, J12.4, J12.14, J13.4, J13.14, SW1.C, SW2.C, SW3.C, SW4.C; also elsewhere on the board
unnamed: D8.1 (K), SW1.S1
unnamed: D9.1 (K), SW2.S1
unnamed: D10.1 (K), SW3.S1
unnamed: D11.1 (K), SW4.S1
unnamed: J7.2, J12.2
unnamed: J12.3, J13.2
unnamed: R23.2, R31.2, SW1.B
unnamed: R24.1, R25.2, SW1.A
unnamed: R32.2, R34.2, SW2.B
unnamed: R33.1, R35.2, SW2.A
unnamed: R36.2, R38.2, SW4.B
unnamed: R37.1, R39.2, SW4.A
unnamed: R42.2, R44.2, SW3.B
unnamed: R43.1, R45.2, SW3.A

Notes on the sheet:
LEFT ENCODER
RIGHT SIDE BUTTONS
LEFT SIDE BUTTONS
RIGHT TOP BUTTONS
LEFT TOP BUTTONS
RIGHT ENCODER
RPM CAHSER LEDS

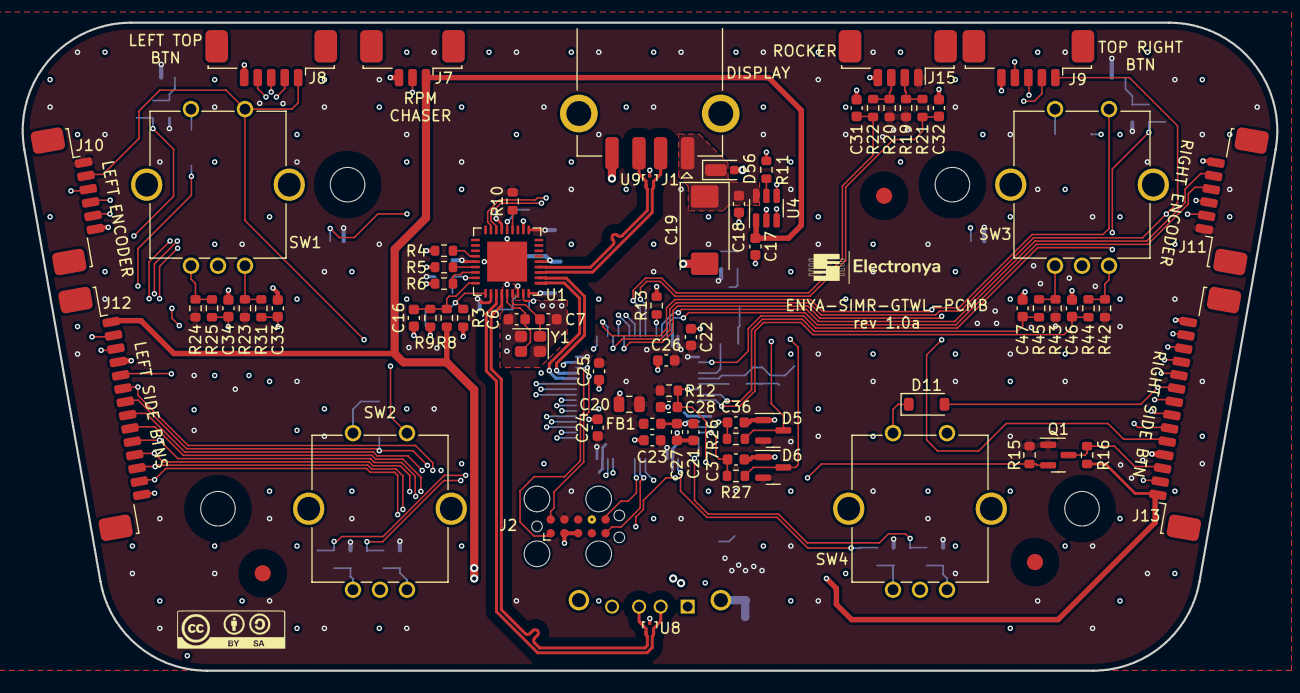
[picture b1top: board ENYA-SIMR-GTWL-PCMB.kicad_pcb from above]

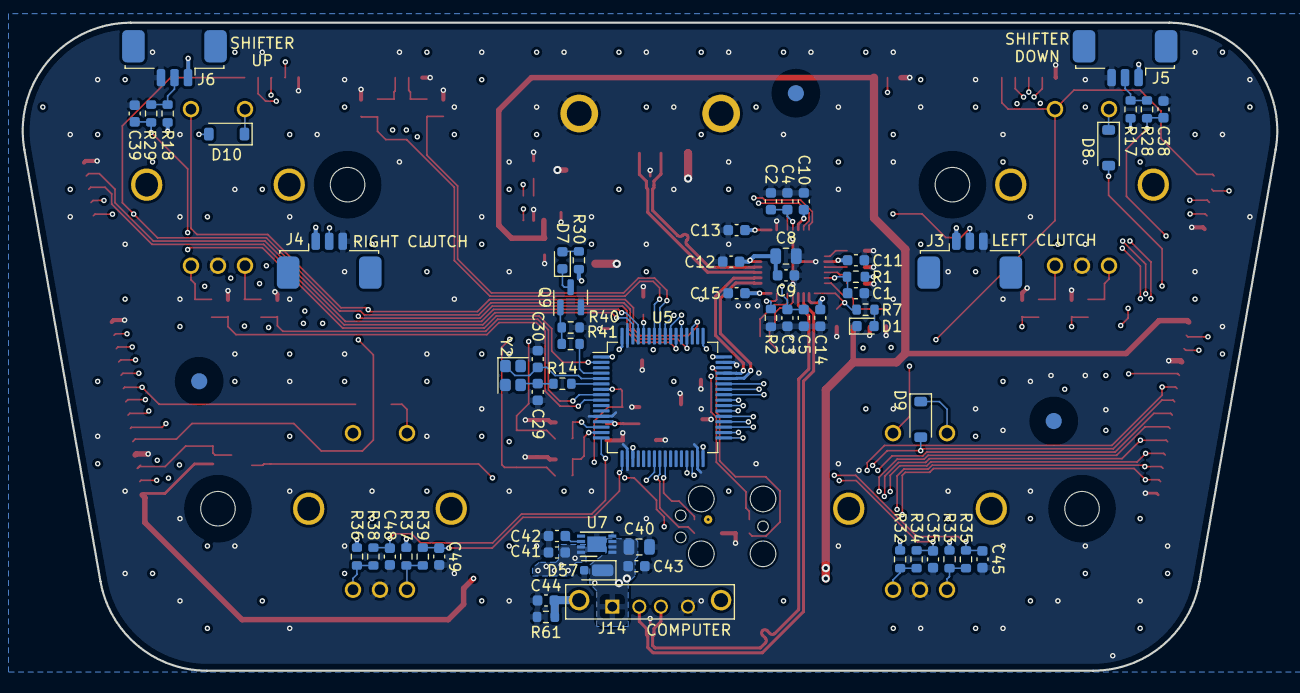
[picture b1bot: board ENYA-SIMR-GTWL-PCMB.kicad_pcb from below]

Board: 4 copper layers, 116.2 x 60.0 mm, 147 parts (64 on the bottom side), 94 nets.

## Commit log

2023-06-23 project creation
2023-06-29 schematic + PCB done. ready to tag and order
2023-06-30 rework planes + adding step file
2023-06-30 updating gitignore
2023-07-01 using only one diode per selector switch + adding ferrite on VDDA
2023-10-08 rework for encoder instead of selector switch

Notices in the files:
parts and their libraries:
CC-BY-SA, creative common
